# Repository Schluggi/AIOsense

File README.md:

# AIOsense

## Description
Based on the idea of an all-in-one sensor AIOsense was born.

The goal is to provide you with a sensor that is modular, affordable and
easy to solder (no SMD) as an alternative for commercially available sensors. We
also focus on upgrade-ability, so you don't have to buy all parts again in case
of a new PCB release. In most cases, this sensor is cheaper and better than the
commercially ones. 

## Available Sensors / Modules

- (RGB)-LED
- Barometer
- Breath VOC equivalent
- Buzzer / Beeper
- CO² equivalent
- Humidity sensor
- Light / Illumination sensor
- PIR motion sensor
- Temperature sensor
- mmWave / Radar sensor

**Coming soon:**
- Full Voice Assistant support
- Microphone
- Speaker

All supported sensors & modules are listed in the documentation:
[Sensor Modules](https://aiosense.readthedocs.io/en/latest/sensors/)

## What does it look like? 👀

| Without lid                        | With lid                             |
|------------------------------------|--------------------------------------|
|  |  |

> **Note:** The PCB in this image is not fully equipped either is this the final case
> design ([issue](https://github.com/Schluggi/AIOsense/issues/9)).

### Rendered images

| 3D                          | 2D                       |
|-----------------------------|--------------------------|
|  |  |

### Schematic

You can find the schematic [here](schematic/AIOsense.pdf).

## Power consumption

The power consumption depends on your configuration. On a fully equipped Board (ESP32-C3 + mmWave + PIR + BME280 +
LightSensor) we measured an idle power consumption of **0.45W / 0.09A** some peaks around **0.78W / 0.15A**.

Without a mmWave sensor the idle power consumption is around **0.11W / 0.02A** and peak near **0.45W / 0.09A**.

## How to start

You want to make your own AIOsense?<br>
Let's jump right into the [documentation](https://aiosense.readthedocs.io/en/latest/quickstart/).

## Questions?

Just open an [issue](https://github.com/Schluggi/AIOsense/issues/new) :)

## Credits & Special thanks

Created and maintained by Lukas Schulte-Tickmann / [Schluggi](https://github.com/Schluggi).

### Special thanks
- My dad for some electrical engineering advice and PCB reviewing
- [lukas-holzner](https://github.com/lukas-holzner) for the case design and some general discussions about the board
- [jankae](https://github.com/jankae) for PCB reviewing
- [reschandreas](https://github.com/reschandreas) for general repo work
- [PCBWay³](https://pcbway.com/g/DFb536) for sponsoring the PCB prototypes

### Contributors

<br>

Inspired by [EverythingSmartHome](https://everythingsmarthome.co.uk/).

<hr>
³ Affiliate link

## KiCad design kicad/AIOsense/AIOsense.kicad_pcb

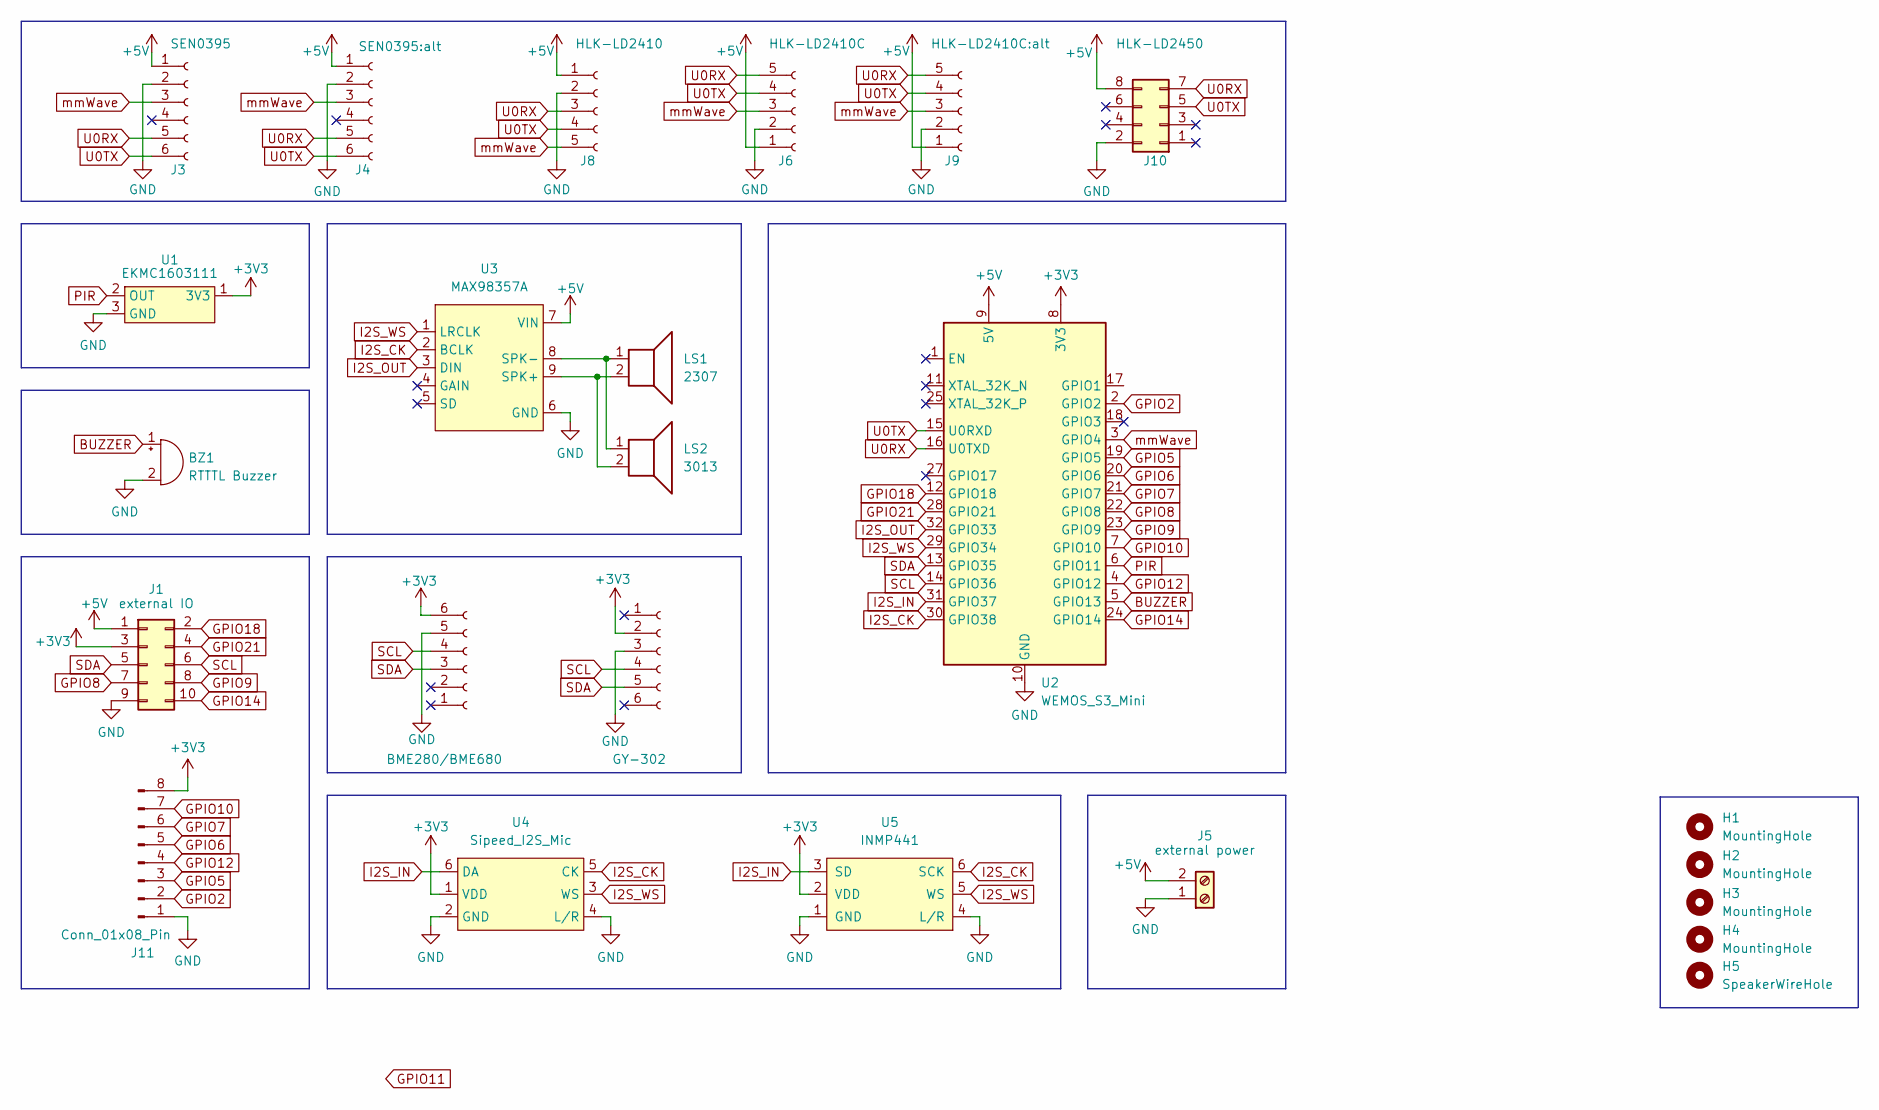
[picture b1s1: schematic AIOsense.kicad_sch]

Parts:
BZ1: RTTTL Buzzer; Buzzer_D12mm_P6.5mm
H1, H2, H3, H4: MountingHole; MountingHole_3.2mm_M3_DIN965_Pad
H5: SpeakerWireHole; Hole_Unplated_3.0mm
J1: external IO; PinHeader_2x05_P2.54mm_Vertical
J2: GY-302; PinSocket_1x06_P2.54mm_Vertical
J3: SEN0395; PinSocket_1x06_P2.54mm_Vertical; Manufacturer_Part_Number SEN0395; Digikey Part # 1738-SEN0395-ND
J4: SEN0395:alt; PinSocket_1x06_P2.54mm_Vertical; Manufacturer_Part_Number SEN0395; Digikey Part # 1738-SEN0395-ND
J5: external power; TerminalBlock_TE_282834-2_1x02_P2.54mm_Horizontal; Manufacturer_Part_Number 691210910002; Digikey Part # 732-691210910002-ND
J6: HLK-LD2410C; PinSocket_1x05_P2.54mm_Vertical; Manufacturer_Part_Number LD2410; Digikey Part # /
J7: BME280/BME680; PinSocket_1x06_P2.54mm_Vertical
J8: HLK-LD2410; PinSocket_1x05_P1.27mm_Vertical; Manufacturer_Part_Number LD2410; Digikey Part # /
J9: HLK-LD2410C:alt; PinSocket_1x05_P2.54mm_Vertical; Manufacturer_Part_Number LD2410; Digikey Part # /
J10: HLK-LD2450; PinSocket_2x04_P2.00mm_Vertical
J11: Conn_01x08_Pin; PinHeader_1x08_P2.54mm_Vertical
LS1: 2307; Speaker_2307
LS2: 3013; Speaker_3013
U1: EKMC1603111; PIR_EKMC1603111_TO-5; Manufacturer_Part_Number EKMC1603111; Digikey Part # 255-3086-ND
U2: WEMOS_S3_Mini
U3: MAX98357A; Adafruit_MAX98357A
U4: Sipeed_I2S_Mic
U5: INMP441; Manufacturer_Part_Number INMP441ACEZ-R7; Digikey Part # obsolete

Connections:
+3V3: J1.3, J2.2, J7.6, J11.8, U1.1 (3V3), U2.8 (3V3), U4.1 (VDD), U5.2 (VDD)
+5V: J1.1, J3.1, J4.1, J5.2, J6.1, J8.1, J9.1, J10.8, U2.9 (5V), U3.7 (VIN)
BUZZER: BZ1.1 (-), U2.5 (GPIO13)
GND: BZ1.2 (+), J1.9, J2.3, J3.2, J4.2, J5.1, J6.2, J7.5, J8.2, J9.2, J10.2, J11.1, U1.3 (GND), U2.10 (GND), U2.26 (GND), U3.6 (GND), U4.2 (GND), U4.4 (L/R), U5.1 (GND), U5.4 (L/R)
GPIO2: J11.2, U2.2 (GPIO2)
GPIO5: J11.3, U2.19 (GPIO5)
GPIO6: J11.5, U2.20 (GPIO6)
GPIO7: J11.6, U2.21 (GPIO7)
GPIO8: J1.7, U2.22 (GPIO8)
GPIO9: J1.8, U2.23 (GPIO9)
GPIO10: J11.7, U2.7 (GPIO10)
GPIO12: J11.4, U2.4 (GPIO12)
GPIO14: J1.10, U2.24 (GPIO14)
GPIO18: J1.2, U2.12 (GPIO18)
GPIO21: J1.4, U2.28 (GPIO21)
I2S_CK: U2.30 (GPIO38), U3.2 (BCLK), U4.5 (CK), U5.6 (SCK)
I2S_IN: U2.31 (GPIO37), U4.6 (DA), U5.3 (SD)
I2S_OUT: U2.32 (GPIO33), U3.3 (DIN)
I2S_WS: U2.29 (GPIO34), U3.1 (LRCLK), U4.3 (WS), U5.5 (WS)
unnamed: LS1.2, LS2.2, U3.9 (SPK+)
unnamed: LS1.1, LS2.1, U3.8 (SPK-)
PIR: U1.2 (OUT), U2.6 (GPIO11)
SCL: J1.6, J2.4, J7.4, U2.14 (GPIO36)
SDA: J1.5, J2.5, J7.3, U2.13 (GPIO35)
U0RX: J3.5, J4.5, J6.5, J8.3, J9.5, J10.7, U2.16 (U0TXD)
U0TX: J3.6, J4.6, J6.4, J8.4, J9.4, J10.5, U2.15 (U0RXD)
mmWave: J3.3, J4.3, J6.3, J8.5, J9.3, U2.3 (GPIO4)

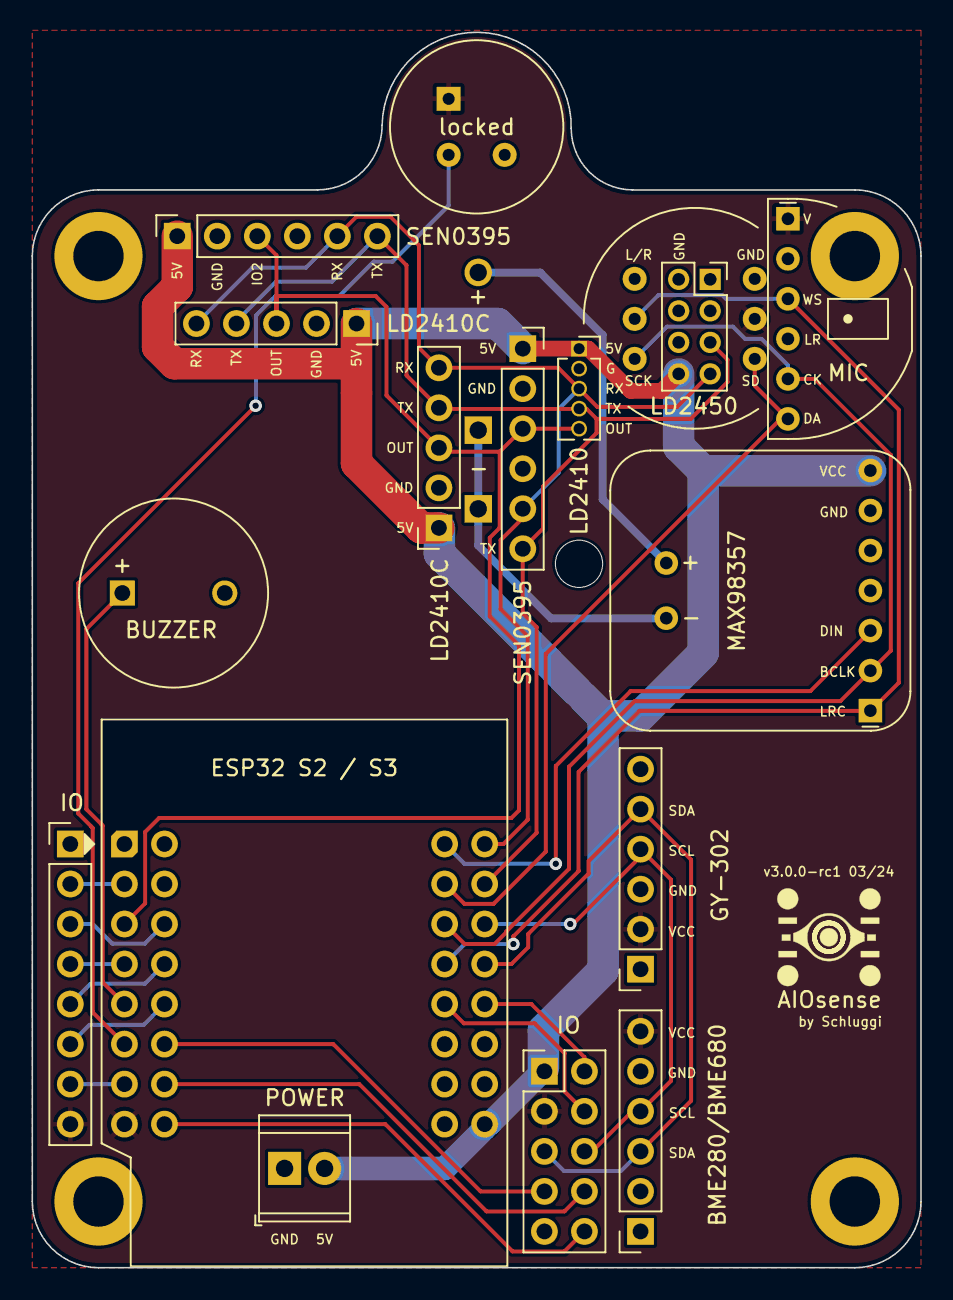
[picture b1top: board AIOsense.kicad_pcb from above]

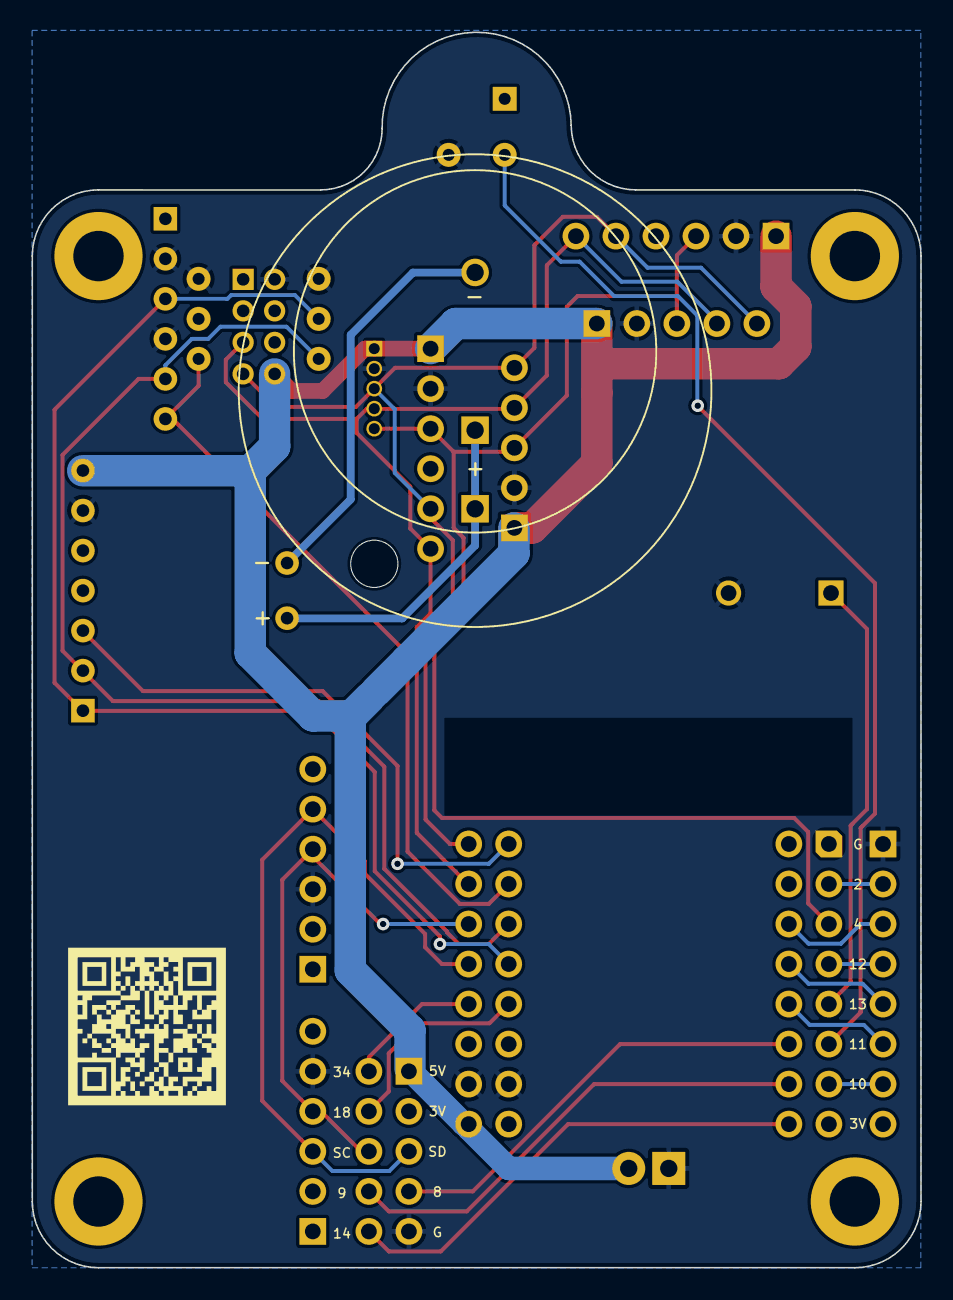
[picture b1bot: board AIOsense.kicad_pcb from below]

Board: 2 copper layers, 56.4 x 78.4 mm, 24 parts (2 on the bottom side), 27 nets.

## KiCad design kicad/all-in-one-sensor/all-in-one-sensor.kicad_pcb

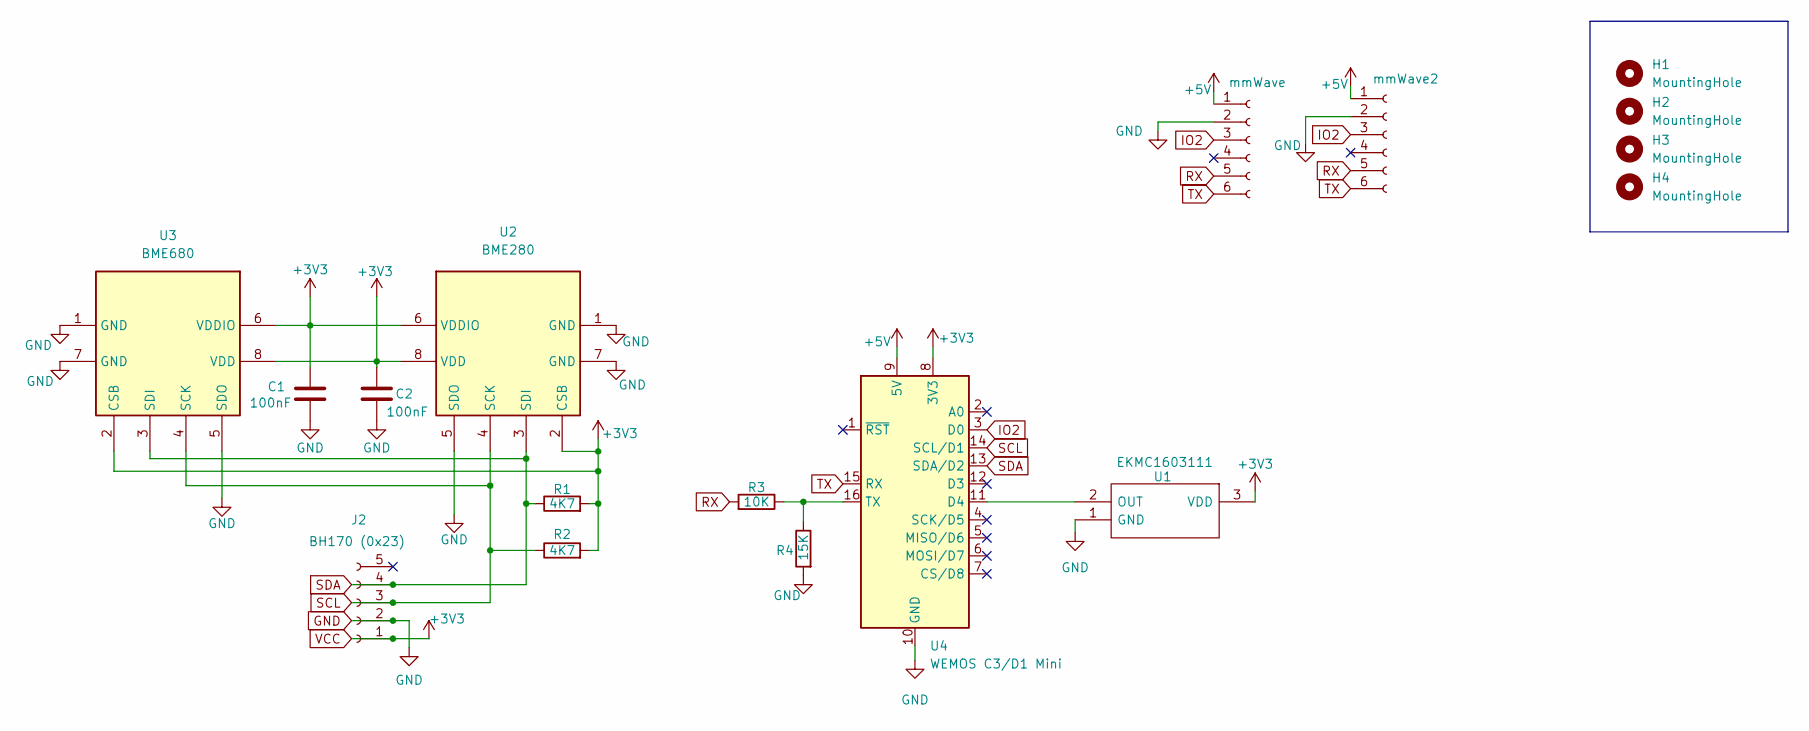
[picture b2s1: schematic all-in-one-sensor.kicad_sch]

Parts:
C1, C2: 100nF; C_Disc_D5.0mm_W2.5mm_P2.50mm
H1, H2, H3, H4: MountingHole; MountingHole_3.2mm_M3
J2: BH170 (0x23); PinSocket_1x05_P2.54mm_Vertical
J3: mmWave; PinSocket_1x06_P2.54mm_Vertical
J4: mmWave2; PinSocket_1x06_P2.54mm_Vertical
R1, R2: 4K7; R_Axial_DIN0207_L6.3mm_D2.5mm_P10.16mm_Horizontal
R3: 10K; R_Axial_DIN0207_L6.3mm_D2.5mm_P10.16mm_Horizontal
R4: 15K; R_Axial_DIN0207_L6.3mm_D2.5mm_P10.16mm_Horizontal
U1: EKMC1603111; EKMB1193111; Mouser Part Number 769-EKMC1603111
U2: BME280; Bosch_LGA-8_2.5x2.5mm_P0.65mm_ClockwisePinNumbering
U3: BME680; Bosch_LGA-8_3x3mm_P0.8mm_ClockwisePinNumbering
U4: WEMOS C3/D1 Mini; WEMOS_D1_mini_light

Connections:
+5V: J3.1, J4.1, U4.9 (5V)
GND: C1.2, C2.2, J2.2, J3.2, J4.2, R4.2, U1.1 (GND), U2.1 (GND), U2.5 (SDO), U2.7 (GND), U3.1 (GND), U3.5 (SDO), U3.7 (GND), U4.10 (GND)
IO2: J3.3, J4.3, U4.3 (D0)
unnamed: R3.1, R4.1, U4.16 (TX)
unnamed: U1.2 (OUT), U4.11 (D4)
RX: J3.5, J4.5, R3.2
SCL: J2.3, R2.1, U2.4 (SCK), U3.4 (SCK), U4.14 (SCL/D1)
SDA: J2.4, R1.1, U2.3 (SDI), U3.3 (SDI), U4.13 (SDA/D2)
TX: J3.6, J4.6, U4.15 (RX)
VCC: C1.1, C2.1, J2.1, R1.2, R2.2, U1.3 (VDD), U2.2 (CSB), U2.6 (VDDIO), U2.8 (VDD), U3.2 (CSB), U3.6 (VDDIO), U3.8 (VDD), U4.8 (3V3)

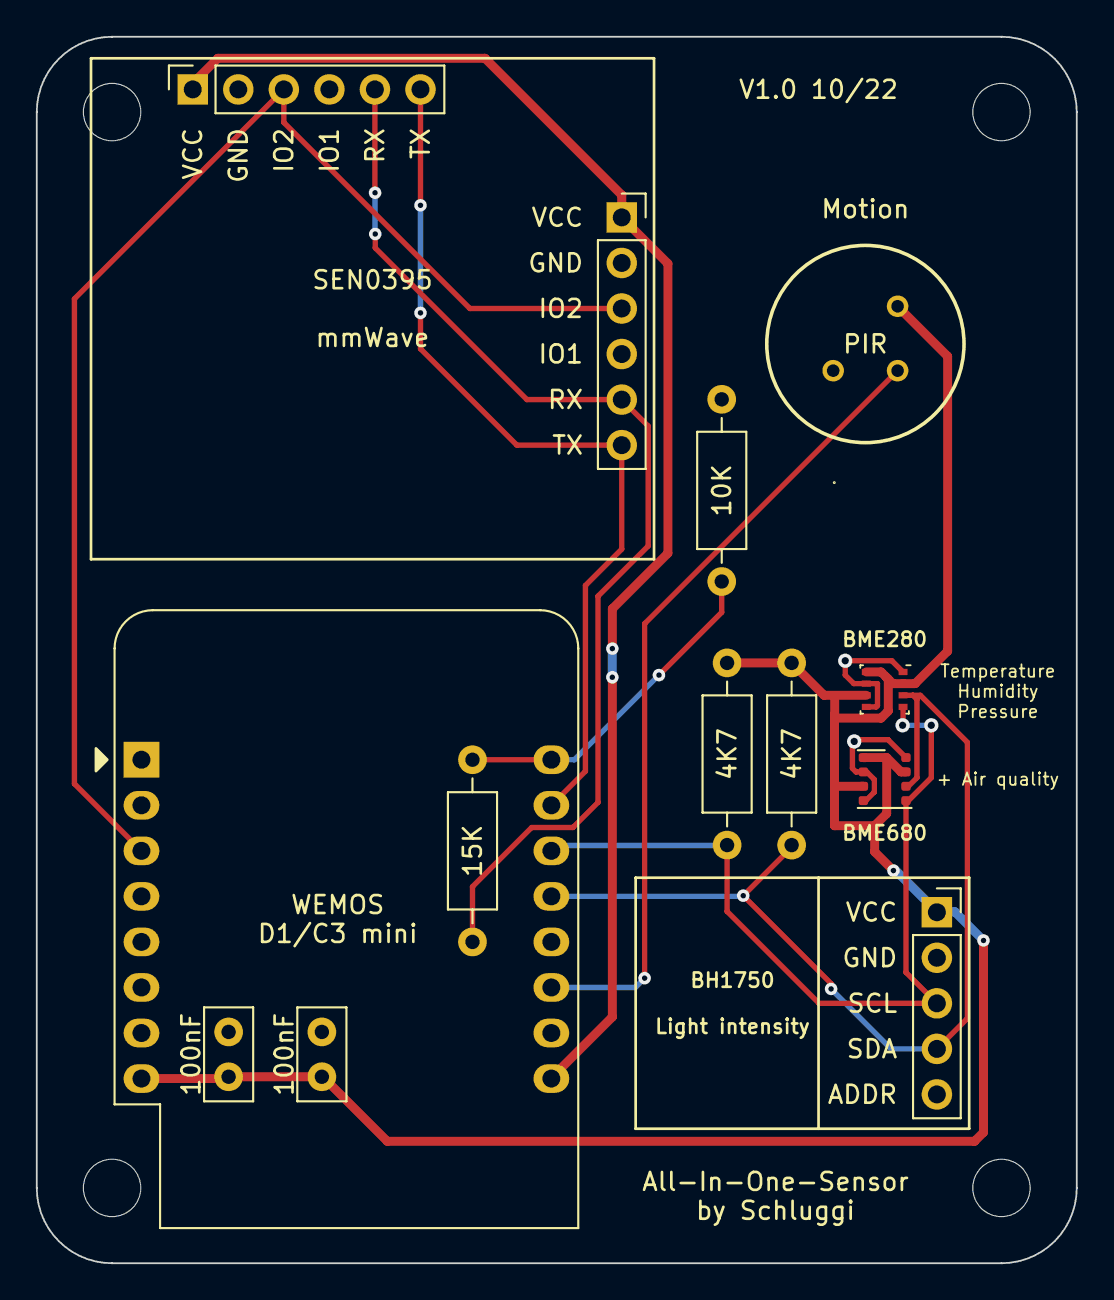
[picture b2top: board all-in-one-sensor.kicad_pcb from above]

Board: 2 copper layers, 58.0 x 68.4 mm, 17 parts (0 on the bottom side), 10 nets.

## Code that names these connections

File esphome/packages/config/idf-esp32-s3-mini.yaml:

substitutions:
  buzzer_pin: GPIO13
  i2s_bclk_pin: GPIO38
  i2s_din_pin: GPIO37
  i2s_dout_pin: GPIO33
  i2s_lrclk_pin: GPIO10
  pir_pin: GPIO11
  rgb_led_pin: GPIO47
  rgb_led_type: RGB
  sen0395_io_pin: GPIO4
  uart_rx_pin: GPIO44
  uart_tx_pin: GPIO43

esp32:
  board: lolin_s3_mini
  variant: esp32s3
  flash_size: 4MB

  framework:
    type: esp-idf

i2c:
  sda: GPIO35
  scl: GPIO36

sensor:
  - platform: internal_temperature
    name: "CPU Temperature"

psram:
  mode: octal
  speed: 80MHz

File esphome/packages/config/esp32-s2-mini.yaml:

substitutions:
  buzzer_pin: GPIO9
  i2s_bclk_pin: GPIO36    # SCK
  i2s_din_pin: GPIO38     # mic
  i2s_dout_pin: GPIO40    # speaker
  i2s_lrclk_pin: GPIO34   # WS
  led_invert: "true"
  led_pin: GPIO15
  pir_pin: GPIO11
  sen0395_io_pin: GPIO5
  uart_rx_pin: GPIO37
  uart_tx_pin: GPIO39

esp32:
  board: lolin_s2_mini
  flash_size: 4MB
  framework:
    type: esp-idf
    version: recommended

i2c:
  sda: GPIO33
  scl: GPIO35

sensor:
  - platform: internal_temperature
    name: "CPU Temperature"

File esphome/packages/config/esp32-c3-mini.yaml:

substitutions:
  buzzer_pin: A0
  i2s_bclk_pin: A1
  i2s_lrclk_pin: A5
  pir_pin: A4
  rgb_led_pin: GPIO7
  rgb_led_type: GRB
  sen0395_io_pin: A2
  uart_rx_pin: GPIO20
  uart_tx_pin: GPIO21
  led_invert: "false"

esphome:
  platformio_options:
    board_build.extra_flags:
      - "-DARDUINO_USB_CDC_ON_BOOT=0"
    board_build.flash_mode: dio

esp32:
  board: lolin_c3_mini
  flash_size: 4MB
  framework:
    type: esp-idf
    version: recommended

wifi:
  output_power: 8.5dBm

i2c:
  sda: GPIO8
  scl: GPIO10

sensor:
  - platform: internal_temperature
    name: "CPU Temperature"

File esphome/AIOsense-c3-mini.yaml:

substitutions:
  name: aiosense-c3-mini  # name of this device

esphome:
  name: "${name}"
  platformio_options:
    board_build.flash_mode: dio

esp32:
  board: esp32-c3-devkitm-1
  framework:
    type: esp-idf

# Enable logging
logger:
  baud_rate: 0 # disable logging via UART

# Enable Home Assistant API
api:
  encryption:
    key: "<secret>"

ota:
  password: "<secret>"

wifi:
  ssid: !secret wifi_ssid
  password: !secret wifi_password
  output_power: 8.5dBm
#  manual_ip:
#    static_ip: 192.168.1.111
#    subnet: 255.255.255.0
#    gateway: 192.168.1.1

bluetooth_proxy:

i2c:
  sda: GPIO8
  scl: GPIO10
  scan: true

uart:
  id: uart_bus
  tx_pin: GPIO21
  rx_pin: GPIO20
  baud_rate: 115200
#  debug:
#    direction: BOTH
#    dummy_receiver: true
#    after:
#      delimiter: "\n"
#    sequence:
#      - lambda: UARTDebug::log_string(direction, bytes);

binary_sensor:
  - platform: gpio
    name: "${name} PIR"
    id: motion_pir
    pin: GPIO6
    device_class: motion

  - platform: gpio
    name: "${name} mmWave"
    id: motion_mmwave
    device_class: occupancy
    pin:
      number: GPIO2
      mode: INPUT_PULLDOWN

  - platform: template
    name: ${name} Occupancy
    id: occupancy
    device_class: occupancy
    lambda: |-
      if (id(motion_mmwave).state or id(motion_pir).state) {
        return true;
      } 
      else if (id(motion_mmwave).state == 0 and id(motion_pir).state == 0) {
        return false;
      } 
      else {
        return id(occupancy).state;
      }

sensor:
  - platform: bh1750
    name: "${name} Illuminance"
    address: 0x23
    update_interval: 5s

  - platform: bme280 # or bme680
    address: 0x76
    update_interval: 60s
    temperature:
      name: "${name} Temperature"
      filters:
        offset: -2.5
    pressure:
      name: "${name} Pressure"
    humidity:
      name: "${name} Humidity"
  #   gas_resistance: # bme680 only
  #     name: "${name} Gas Resistance"

switch:
  - platform: template
    name: "${name} mmWave Sensor"
    id: "mmwave_sensor"
    optimistic: true
    restore_state: true
    assumed_state: true
    turn_on_action:
      - uart.write: "sensorStart"
      - delay: 1s
    turn_off_action:
      - uart.write: "sensorStop"
      - delay: 1s

  - platform: template
    name: "${name} mmWave LED"
    id: "mmwave_led"
    optimistic: true
    restore_state: true
    assumed_state: true
    turn_on_action:
      - switch.turn_off: mmwave_sensor
      - delay: 1s
      - uart.write: "setLedMode 1 0"
      - delay: 1s
      - uart.write: "saveConfig"
      - delay: 3s
      - switch.turn_on: mmwave_sensor
    turn_off_action:
      - switch.turn_off: mmwave_sensor
      - delay: 1s
      - uart.write: "setLedMode 1 1"
      - delay: 1s
      - uart.write: "saveConfig"
      - delay: 3s
      - switch.turn_on: mmwave_sensor

number:
  - platform: template
    name: "${name} mmWave Distance"
    id: mmwave_distance
    min_value: 0
    max_value: 800
    initial_value: 315
    optimistic: true
    step: 15
    restore_value: true
    unit_of_measurement: cm
    mode: box
    set_action:
      - switch.turn_off: mmwave_sensor
      - delay: 1s
      - uart.write: !lambda int cm = (int)ceil(x / 15.0);
          std::string cms = "detRangeCfg -1 0 " + to_string(cm);
          return std::vector<unsigned char>(cms.begin(), cms.end());
      - delay: 1s
      - uart.write: "saveCfg 0x45670123 0xCDEF89AB 0x956128C6 0xDF54AC89"
      - delay: 1s
      - switch.turn_on: mmwave_sensor

  - platform: template
    name: "${name} mmWave Off Latency"
    id: mmwave_latency
    min_value: 0
    max_value: 65000
    initial_value: 12500
    optimistic: true
    step: 25
    restore_value: true
    unit_of_measurement: ms
    mode: box
    set_action:
      - switch.turn_off: mmwave_sensor
      - delay: 1s
      - uart.write: !lambda int ms = (int)ceil(x / 25.0);
          std::string mss = "outputLatency -1 0 " + to_string(ms);
          return std::vector<unsigned char>(mss.begin(), mss.end());
      - delay: 1s
      - uart.write: "saveCfg 0x45670123 0xCDEF89AB 0x956128C6 0xDF54AC89"
      - delay: 1s
      - switch.turn_on: mmwave_sensor

  - platform: template
    name: "${name} mmWave Sensitivity"
    id: mmwave_sensitivity
    min_value: 0
    max_value: 9
    initial_value: 7
    optimistic: true
    step: 1
    restore_value: true
    set_action:
      - switch.turn_off: mmwave_sensor
      - delay: 1s
      - uart.write:
          !lambda std::string mss = "setSensitivity " + to_string((int)x);
          return std::vector<unsigned char>(mss.begin(), mss.end());
      - delay: 1s
      - uart.write: "saveConfig"
      - delay: 1s
      - switch.turn_on: mmwave_sensor

button:
  - platform: restart
    name: "${name} Restart"

  - platform: template
    name: "${name} Factory Reset mmWave"
    on_press:
      - switch.turn_off: mmwave_sensor
      - delay: 1s
      - uart.write: "resetCfg"
      - delay: 3s
      - switch.turn_on: mmwave_sensor

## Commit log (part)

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2025-09-04 chore(deps): update pip requirements using pip-compile
2025-09-05 chore(deps): update dependency markdown to v3.9 (#390)
2025-09-05 chore(deps): update dependency backrefs to v6
2025-09-05 chore(deps): update pip requirements using pip-compile (#391)
2025-09-07 chore(deps): update dependency mkdocs-material to v9.6.19
2025-09-08 chore(deps): update dependency mkdocs-material to v9.6.19 (#392)
2025-09-08 chore(deps): update pip requirements using pip-compile (#393)
2025-09-15 chore(deps): update dependency mkdocs-material to v9.6.20
2025-09-16 chore(deps): update dependency mkdocs-material to v9.6.20 (#394)
2025-09-16 chore(deps): update pip requirements using pip-compile (#395)
2025-09-19 chore(deps): update pip requirements using pip-compile (#397)
2025-09-19 chore(deps): update dependency click to v8.3.0
2025-09-25 chore(deps): update dependency pyyaml to v6.0.3
2025-09-26 chore(deps): update dependency pyyaml to v6.0.3 (#398)
2025-09-27 chore: update esp-idf framework version from latest to recommended
    Switched ESP-IDF framework version from 'latest' to 'recommended' across all ESP32 mini configurations to resolve ESPhome error
2025-09-27 fix: update LED configuration to use output reference
    Replace direct pin configuration with output reference.
2025-09-27 chore(deps): update dependency markupsafe to v3.0.3
2025-09-28 chore(deps): update dependency markupsafe to v3.0.3 (#399)
2025-09-30 chore(deps): update dependency mkdocs-material to v9.6.21
2025-10-01 chore(deps): update dependency mkdocs-material to v9.6.21 (#400)
2025-10-01 chore(deps): update dependency click to v8.3.0 (#396)
2025-10-05 chore(deps): update dependency certifi to v2025.10.5
2025-10-05 chore(deps): update dependency certifi to v2025.10.5 (#401)
2025-10-08 chore(deps): update dependency platformdirs to v4.5.0
2025-10-08 chore(deps): update dependency platformdirs to v4.5.0 (#402)
2025-10-12 chore(deps): update dependency idna to v3.11
2025-10-12 chore(deps): update dependency idna to v3.11 (#403)
2025-10-14 chore(deps): update dependency charset-normalizer to v3.4.4
2025-10-14 chore(deps): update dependency charset-normalizer to v3.4.4 (#404)
2025-10-15 chore(deps): update dependency mkdocs-material to v9.6.22 (#405)
2025-11-01 chore(deps): update dependency mkdocs-material to v9.6.23
2025-11-01 chore(deps): update dependency mkdocs-material to v9.6.23 (#406)
2025-11-03 chore(deps): update dependency markdown to v3.10
2025-11-04 chore(deps): update dependency markdown to v3.10 (#407)
2025-11-11 chore(deps): update dependency mkdocs-material to v9.7.0
2025-11-11 chore(deps): update dependency mkdocs-material to v9.7.0 (#408)
2025-11-11 chore(deps): update dependency pymdown-extensions to v10.17.1
2025-11-12 chore(deps): update dependency pymdown-extensions to v10.17.1 (#409)
2025-11-12 chore(deps): update dependency certifi to v2025.11.12
2025-11-12 chore(deps): update dependency certifi to v2025.11.12 (#410)
2025-11-12 chore(deps): update dependency backrefs to v6 (#378)
2025-11-15 chore(deps): update dependency backrefs to v6.1
2025-11-15 chore(deps): update dependency backrefs to v6.1 (#411)
2025-11-15 chore(deps): update dependency click to v8.3.1
2025-11-20 chore(deps): update actions/checkout action to v6
2025-11-20 chore(deps): update actions/checkout action to v6 (#413)
2025-11-26 chore(deps): update dependency pymdown-extensions to v10.17.2
2025-11-26 chore(deps): update dependency pymdown-extensions to v10.17.2 (#414)
2025-12-05 chore(deps): update dependency platformdirs to v4.5.1
2025-12-05 chore(deps): update dependency platformdirs to v4.5.1 (#415)
2025-12-05 chore(deps): update dependency urllib3 to v2.6.0
2025-12-05 chore(deps): update dependency urllib3 to v2.6.0 (#416)
2025-12-07 chore(deps): update dependency pymdown-extensions to v10.18
2025-12-08 chore(deps): update dependency pymdown-extensions to v10.18 (#417)
2025-12-08 chore(deps): update dependency urllib3 to v2.6.1
2025-12-09 chore(deps): update dependency urllib3 to v2.6.1 (#418)
2025-12-11 chore(deps): update dependency urllib3 to v2.6.2
2025-12-12 chore(deps): update dependency urllib3 to v2.6.2 (#419)
2025-12-12 chore(deps): update dependency pymdown-extensions to v10.19 (#420)
2025-12-14 chore(deps): update dependency pymdown-extensions to v10.19.1
2025-12-15 chore(deps): update dependency pymdown-extensions to v10.19.1 (#421)
2025-12-18 chore(deps): update dependency mkdocs-material to v9.7.1
2025-12-18 chore(deps): update dependency mkdocs-material to v9.7.1 (#422)
2025-12-31 chore(deps): update dependency pymdown-extensions to v10.20
2026-01-01 chore(deps): update dependency pymdown-extensions to v10.20 (#423)
2026-01-04 chore(deps): update dependency certifi to v2026
2026-01-04 chore(deps): update dependency certifi to v2026 (#424)
2026-01-07 chore(deps): update dependency urllib3 to v2.6.3
2026-01-07 chore(deps): update dependency urllib3 to v2.6.3 (#426)
2026-01-09 chore(deps): update dependency pathspec to v1
2026-01-21 chore(deps): update dependency markdown to v3.10.1
2026-01-22 chore(deps): update dependency markdown to v3.10.1 (#428)
2026-01-22 chore(deps): update dependency packaging to v26 (#429)
2026-01-24 chore(deps): update dependency pymdown-extensions to v10.20.1
2026-01-24 chore(deps): update dependency pymdown-extensions to v10.20.1 (#430)
2026-02-01 chore(deps): update dependency babel to v2.18.0
2026-02-01 chore(deps): update dependency babel to v2.18.0 (#431)
2026-02-09 chore(deps): update dependency markdown to v3.10.2
2026-02-09 chore(deps): update dependency markdown to v3.10.2 (#432)
2026-02-12 chore(deps): update dependency platformdirs to v4.6.0
2026-02-12 chore(deps): update dependency platformdirs to v4.6.0 (#433)
2026-02-13 chore(deps): update dependency platformdirs to v4.7.0
2026-02-13 chore(deps): update dependency platformdirs to v4.7.0 (#434)
2026-02-13 chore(deps): update dependency platformdirs to v4.7.1
2026-02-14 chore(deps): update dependency platformdirs to v4.7.1 (#435)
2026-02-14 chore(deps): update dependency platformdirs to v4.8.0
2026-02-14 chore(deps): update dependency platformdirs to v4.8.0 (#436)
2026-02-14 chore(deps): update dependency platformdirs to v4.9.0 (#437)
2026-02-15 chore(deps): update dependency platformdirs to v4.9.1
2026-02-15 chore(deps): update dependency platformdirs to v4.9.1 (#438)
2026-02-16 chore(deps): update dependency pymdown-extensions to v10.21
2026-02-16 chore(deps): update dependency pymdown-extensions to v10.21 (#439)
2026-02-16 chore(deps): update dependency platformdirs to v4.9.2
2026-02-16 chore(deps): update dependency platformdirs to v4.9.2 (#440)
2026-02-16 chore(deps): update dependency backrefs to v6.2
2026-02-17 chore(deps): update dependency backrefs to v6.2 (#441)
2026-02-18 chore(deps): update dependency mkdocs-material to v9.7.2
2026-02-18 chore(deps): update dependency mkdocs-material to v9.7.2 (#442)
2026-02-24 chore(deps): update dependency mkdocs-material to v9.7.3
2026-02-24 chore(deps): update dependency mkdocs-material to v9.7.3 (#443)
2026-02-25 chore(deps): update dependency certifi to v2026.2.25
2026-03-03 chore(deps): update dependency mkdocs-material to v9.7.4
2026-03-04 chore(deps): update dependency mkdocs-material to v9.7.4 (#446)
2026-03-05 chore(deps): update dependency platformdirs to v4.9.4
2026-03-05 chore(deps): update dependency platformdirs to v4.9.4 (#447)
2026-03-06 chore(deps): update dependency charset-normalizer to v3.4.5
2026-03-06 chore(deps): update dependency charset-normalizer to v3.4.5 (#448)
2026-03-10 chore(deps): update dependency mkdocs-material to v9.7.5
2026-03-10 chore(deps): update dependency mkdocs-material to v9.7.5 (#450)
2026-03-13 chore(deps): update dependency mkdocs-get-deps to v0.2.2
2026-03-15 chore(deps): update dependency charset-normalizer to v3.4.6
2026-03-16 chore(deps): update dependency charset-normalizer to v3.4.6 (#451)
2026-03-19 chore(deps): update dependency mkdocs-material to v9.7.6
2026-03-19 chore(deps): update dependency mkdocs-material to v9.7.6 (#452)
2026-03-25 chore(deps): update dependency requests to v2.33.0
2026-03-25 chore(deps): update dependency requests to v2.33.0 (#453)
2026-03-29 chore(deps): update dependency pymdown-extensions to v10.21.2 (#454)
2026-03-29 chore(deps): update dependency pygments to v2.20.0
2026-03-30 chore(deps): update dependency pygments to v2.20.0 (#455)
2026-03-30 chore(deps): update dependency requests to v2.33.1
2026-03-30 chore(deps): update dependency requests to v2.33.1 (#456)
2026-04-02 chore(deps): update dependency charset-normalizer to v3.4.7
2026-04-02 chore(deps): update dependency charset-normalizer to v3.4.7 (#457)
2026-04-03 chore(deps): update dependency click to v8.3.2
2026-04-04 chore(deps): update dependency click to v8.3.2 (#458)
2026-04-09 chore(deps): update dependency platformdirs to v4.9.6
2026-04-09 chore(deps): update dependency platformdirs to v4.9.6 (#459)
2026-04-15 chore(deps): update dependency packaging to v26.1
2026-04-15 chore(deps): update dependency packaging to v26.1 (#460)
2026-04-21 chore(deps): update dependency idna to v3.12
2026-04-22 chore(deps): update dependency certifi to v2026.4.22
2026-04-22 chore(deps): update dependency certifi to v2026.4.22 (#462)
2026-04-22 chore(deps): update dependency click to v8.3.3
2026-04-23 chore(deps): update dependency click to v8.3.3 (#463)
2026-04-23 chore(deps): update dependency idna to v3.13
2026-04-23 chore(deps): update dependency idna to v3.13 (#464)
2026-04-24 chore(deps): update dependency packaging to v26.2
2026-04-25 chore(deps): update dependency packaging to v26.2 (#465)
2026-04-28 chore(deps): update dependency backrefs to v7
2026-04-28 chore(deps): update dependency backrefs to v7 (#466)
2026-05-07 chore(deps): update dependency urllib3 to v2.7.0
2026-05-08 chore(deps): update dependency urllib3 to v2.7.0 (#467)
2026-05-10 chore(deps): update dependency idna to v3.14
2026-05-11 chore(deps): update dependency idna to v3.14 (#468)
2026-05-12 chore(deps): update dependency requests to v2.34.0 (#469)
2026-05-13 chore(deps): update dependency idna to v3.15
2026-05-13 chore(deps): update dependency idna to v3.15 (#470)
2026-05-13 chore(deps): update dependency pymdown-extensions to v10.21.3
2026-05-13 chore(deps): update dependency pymdown-extensions to v10.21.3 (#471)
2026-05-13 chore(deps): update dependency requests to v2.34.1
2026-05-14 chore(deps): update dependency requests to v2.34.1 (#472)
2026-05-14 chore(deps): update dependency requests to v2.34.2
2026-05-15 chore(deps): update dependency requests to v2.34.2 (#473)
2026-05-17 chore(deps): update dependency click to v8.4.0
2026-05-17 chore(deps): update dependency click to v8.4.0 (#474)
2026-05-20 chore(deps): update dependency certifi to v2026.5.20
2026-05-20 chore(deps): update dependency certifi to v2026.5.20 (#475)
2026-05-22 chore(deps): update dependency idna to v3.16
2026-05-22 chore(deps): update dependency idna to v3.16 (#476)
2026-05-22 chore(deps): update dependency click to v8.4.1 (#477)
2026-05-28 chore(deps): update dependency platformdirs to v4.10.0
2026-05-28 chore(deps): update dependency platformdirs to v4.10.0 (#478)
2026-05-28 chore(deps): update dependency idna to v3.17
2026-05-29 chore(deps): update dependency idna to v3.17 (#479)
2026-06-02 chore(deps): update dependency idna to v3.18
2026-06-02 chore(deps): update dependency idna to v3.18 (#480)
2026-06-17 chore(deps): update dependency certifi to v2026.6.17
2026-06-17 chore(deps): update dependency certifi to v2026.6.17 (#481)
2026-06-18 chore(deps): update actions/checkout action to v7
2026-06-19 chore(deps): update actions/checkout action to v7 (#482)
2026-06-23 chore(deps): update dependency pymdown-extensions to v11
2026-06-23 chore(deps): update dependency pymdown-extensions to v11 (#483)
2026-06-24 chore(deps): update dependency click to v8.4.2
2026-06-28 chore(deps): update dependency bracex to v2.7
2026-06-29 chore(deps): update dependency bracex to v2.7 (#485)
2026-06-30 chore(deps): update dependency wcmatch to v10.2
2026-06-30 chore(deps): update dependency wcmatch to v10.2 (#486)
2026-06-30 chore(deps): update dependency bracex to v3

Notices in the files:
README.md:
License: MIT
